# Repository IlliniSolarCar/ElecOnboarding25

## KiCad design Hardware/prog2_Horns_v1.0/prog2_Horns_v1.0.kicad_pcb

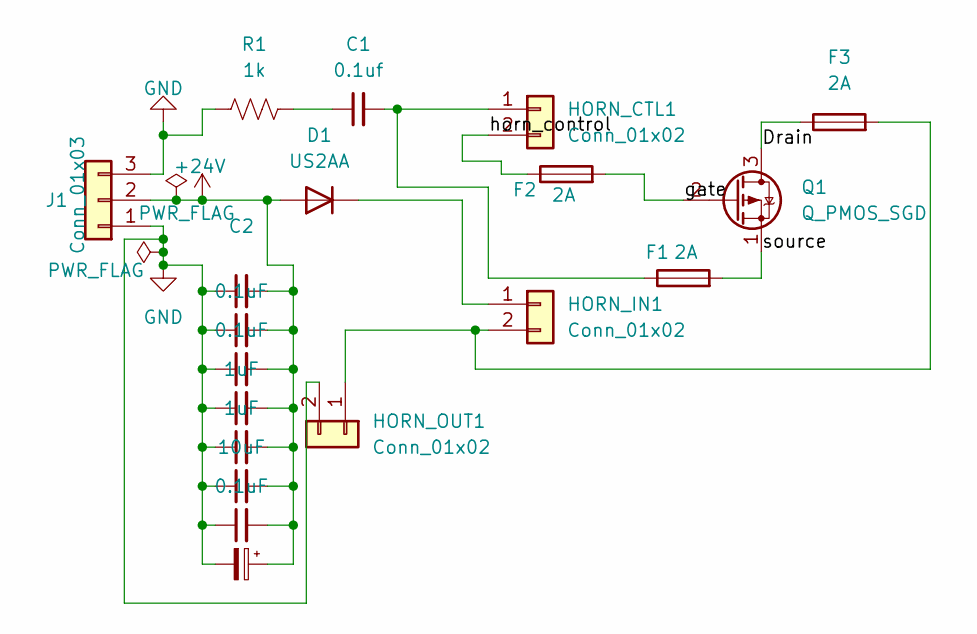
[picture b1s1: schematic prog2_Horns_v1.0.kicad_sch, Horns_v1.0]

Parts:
C1: 0.1uf; CP_Oval_L16.0mm_W8.0mm_P11.5mm
C2: C_Small; CP_Oval_L16.0mm_W8.0mm_P11.5mm
C3, C4, C8: 0.1uF; CP_Oval_L16.0mm_W8.0mm_P11.5mm
C5, C6: 1uF; CP_Oval_L16.0mm_W8.0mm_P11.5mm
C7: 10uF; CP_Oval_L16.0mm_W8.0mm_P11.5mm
C9: 100uF; CP_Radial_D16.5mm_P5.08mm
D1: US2AA; D_SMA; MPN ES2DA-13-F
F1, F2, F3: 2A; Fuse_Littelfuse_1206
HORN_CTL1: Conn_01x02; Molex_CLIK-Mate_502382-0270_1x02-1MP_P1.25mm_Vertical
HORN_IN1: Conn_01x02; Molex_CLIK-Mate_502382-0270_1x02-1MP_P1.25mm_Vertical
HORN_OUT1: Conn_01x02; Molex_CLIK-Mate_502382-0270_1x02-1MP_P1.25mm_Vertical
J1: Conn_01x03; Molex_CLIK-Mate_502382-0370_1x03-1MP_P1.25mm_Vertical
Q1: Q_PMOS_SGD; DirectFET_L4; MPN IRFR010PBF
R1: 1k; R_0805_2012Metric_Pad1.20x1.40mm_HandSolder

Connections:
+24V: C2.2, C3.2, C4.2, C5.2, C6.2, C7.2, C8.2, C9.1, D1.2 (A), J1.2
/Drain: F3.1, Q1.3 (D)
/gate: F2.2, Q1.2 (G)
/horn_control: F2.1, HORN_CTL1.2
/source: F1.2, Q1.1 (S)
GND: C2.1, C3.1, C4.1, C5.1, C6.1, C7.1, C8.1, C9.2, HORN_OUT1.2, J1.1, J1.3, R1.1
unnamed: C1.1, R1.2
unnamed: D1.1 (K), HORN_IN1.1
unnamed: C1.2, F1.1, HORN_CTL1.1
unnamed: F3.2, HORN_IN1.2, HORN_OUT1.1

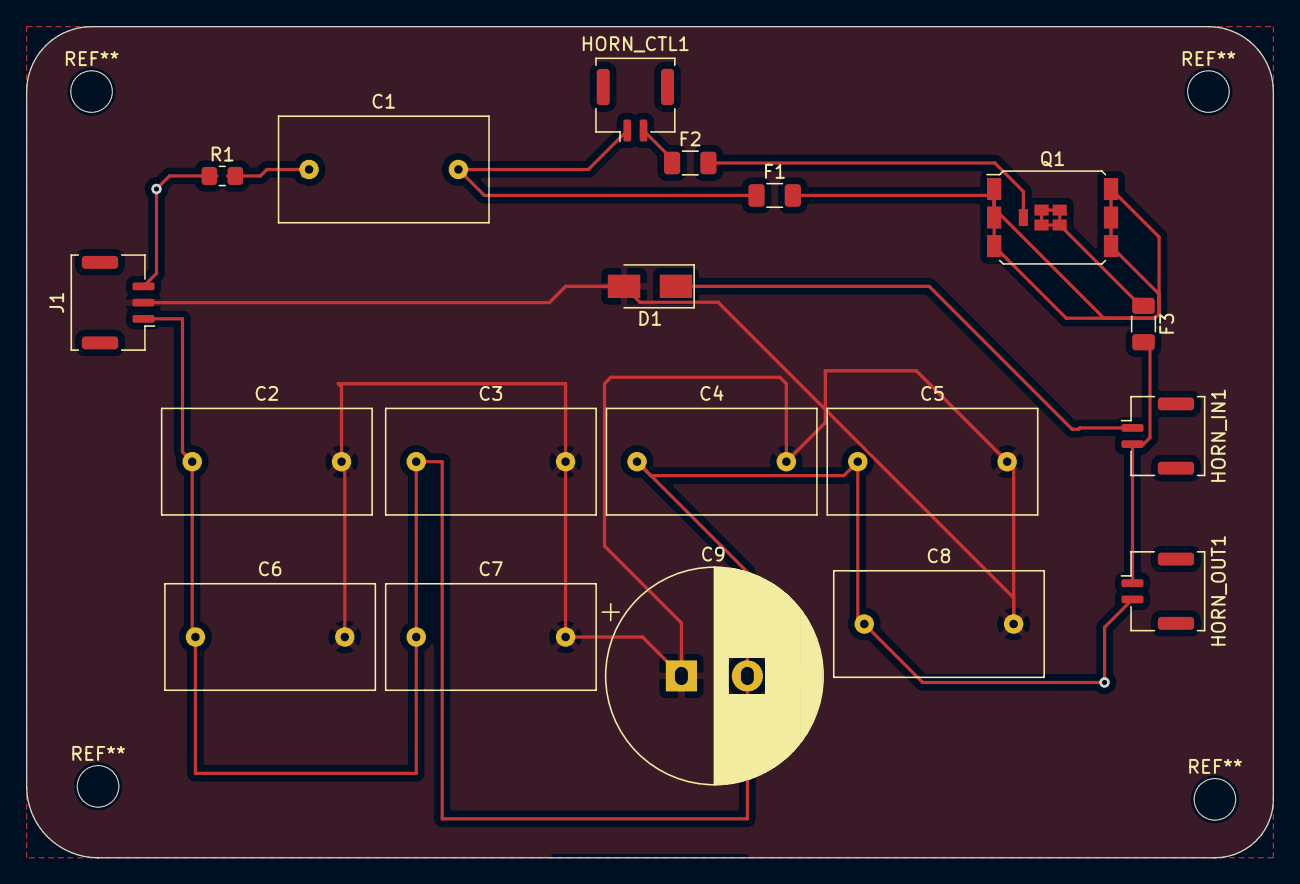
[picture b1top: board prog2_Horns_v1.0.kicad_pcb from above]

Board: 2 copper layers, 96.0 x 64.0 mm, 19 parts (0 on the bottom side), 10 nets.

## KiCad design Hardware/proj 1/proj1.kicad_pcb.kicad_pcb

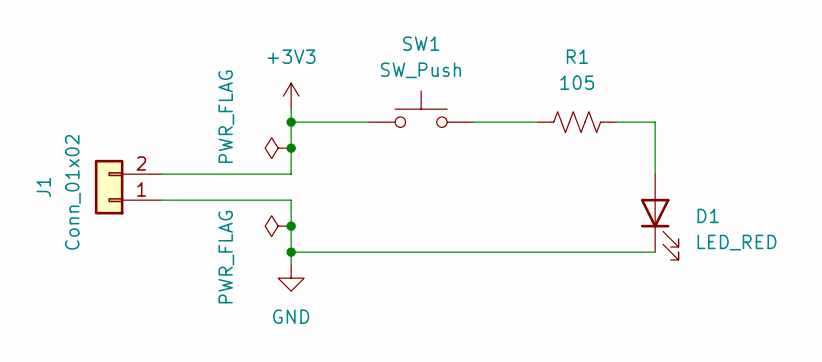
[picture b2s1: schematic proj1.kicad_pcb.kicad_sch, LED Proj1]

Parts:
D1: LED_RED; LED_0603_Symbol_on_F.SilkS
J1: Conn_01x02; Molex_KK-254_AE-6410-02A_1x02_P2.54mm_Vertical
R1: 105; R_0603_1608Metric_Pad0.98x0.95mm_HandSolder
SW1: SW_Push; SW_DIP_SPSTx01_Slide_6.7x4.1mm_W8.61mm_P2.54mm_LowProfile

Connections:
+3V3: J1.2, SW1.1
GND: D1.1 (K), J1.1
unnamed: D1.2 (A), R1.2
unnamed: R1.1, SW1.2

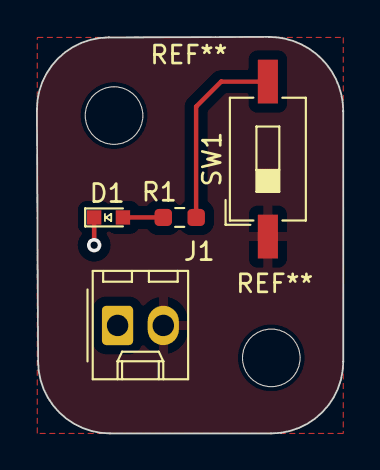
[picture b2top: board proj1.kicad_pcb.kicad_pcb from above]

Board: 2 copper layers, 17.0 x 22.0 mm, 4 parts (0 on the bottom side), 4 nets.
